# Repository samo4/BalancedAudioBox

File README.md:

# BalancedAudioBox

USB connected balanced +4dBu DAC. Also USB powered. And allegedly 384kHz/32bit.

### Background

I have Genelec active speakers that only have balanced +4dBU input. I only use computer (orginally Intel NUC) as source and I wanted a DAC without any extra wires. There are many comercially availible DAC's, but the selection with balanced output is limited and I also wanted USB powered one without any extra features.

### Status

The first prototype is working great, documentation is under construction.

## How to make one

It's an electronics project, so you can use gerbers to make boards, buy components at your favourite distributor, buy [USB to I2S board](https://amanero.com/) or chinese clone, 3D print the enclosure and assemble everything.

STEP files are included, and here's [the link](https://a360.co/3yRnoUF) to Fusion.

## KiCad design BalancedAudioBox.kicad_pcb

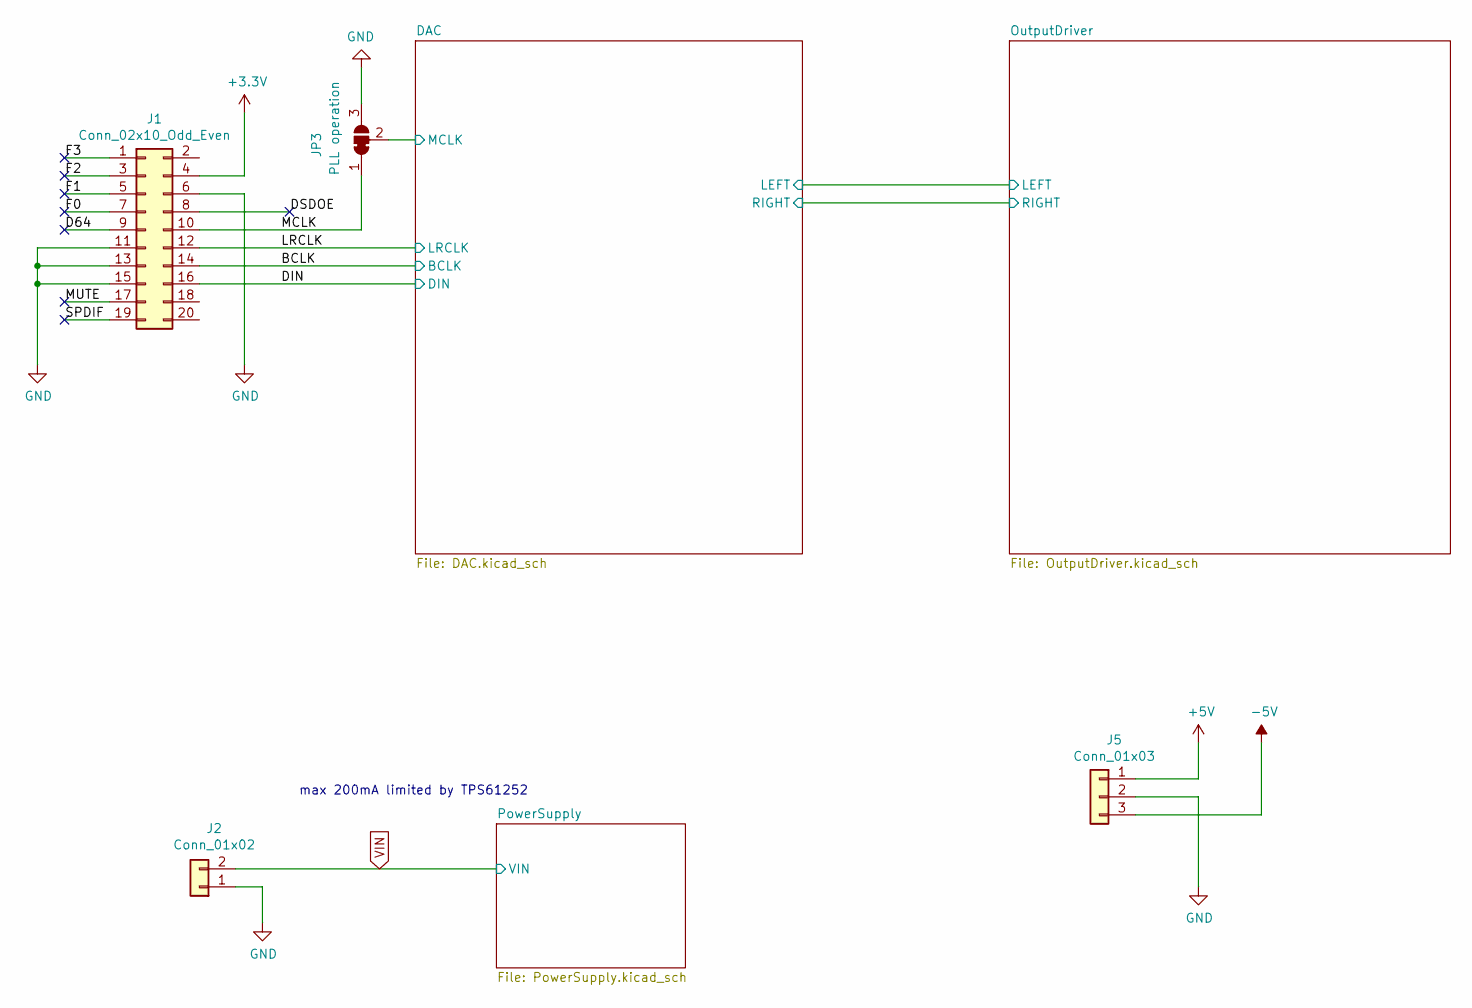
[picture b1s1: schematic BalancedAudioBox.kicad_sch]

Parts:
J1: Conn_02x10_Odd_Even; XMOS_USB_Board_2x10_P2.54mm
J2: Conn_01x02; PinHeader_1x02_P2.54mm_Vertical
J5: Conn_01x03; PinHeader_1x03_P2.54mm_Vertical
JP3: PLL operation; SolderJumper-3_P1.3mm_Bridged12_Pad1.0x1.5mm

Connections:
+3V3: J1.4; also elsewhere on the board
+5V: J5.1; also elsewhere on the board
-5V: J5.3; also elsewhere on the board
/BCLK: J1.14; also elsewhere on the board
/D64: J1.9
/DAC/MCLK: JP3.2 (C); also elsewhere on the board
/DIN: J1.16; also elsewhere on the board
/DSDOE: J1.8
/F0: J1.7
/F1: J1.5
/F2: J1.3
/F3: J1.1
/LRCLK: J1.12; also elsewhere on the board
/MCLK: J1.10, JP3.1 (A)
/MUTE: J1.17
/SPDIF: J1.19
GND: J1.6, J1.11, J1.13, J1.15, J2.1, J5.2, JP3.3 (B); also elsewhere on the board
VIN: J2.2; also elsewhere on the board

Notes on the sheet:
max 200mA limited by TPS61252

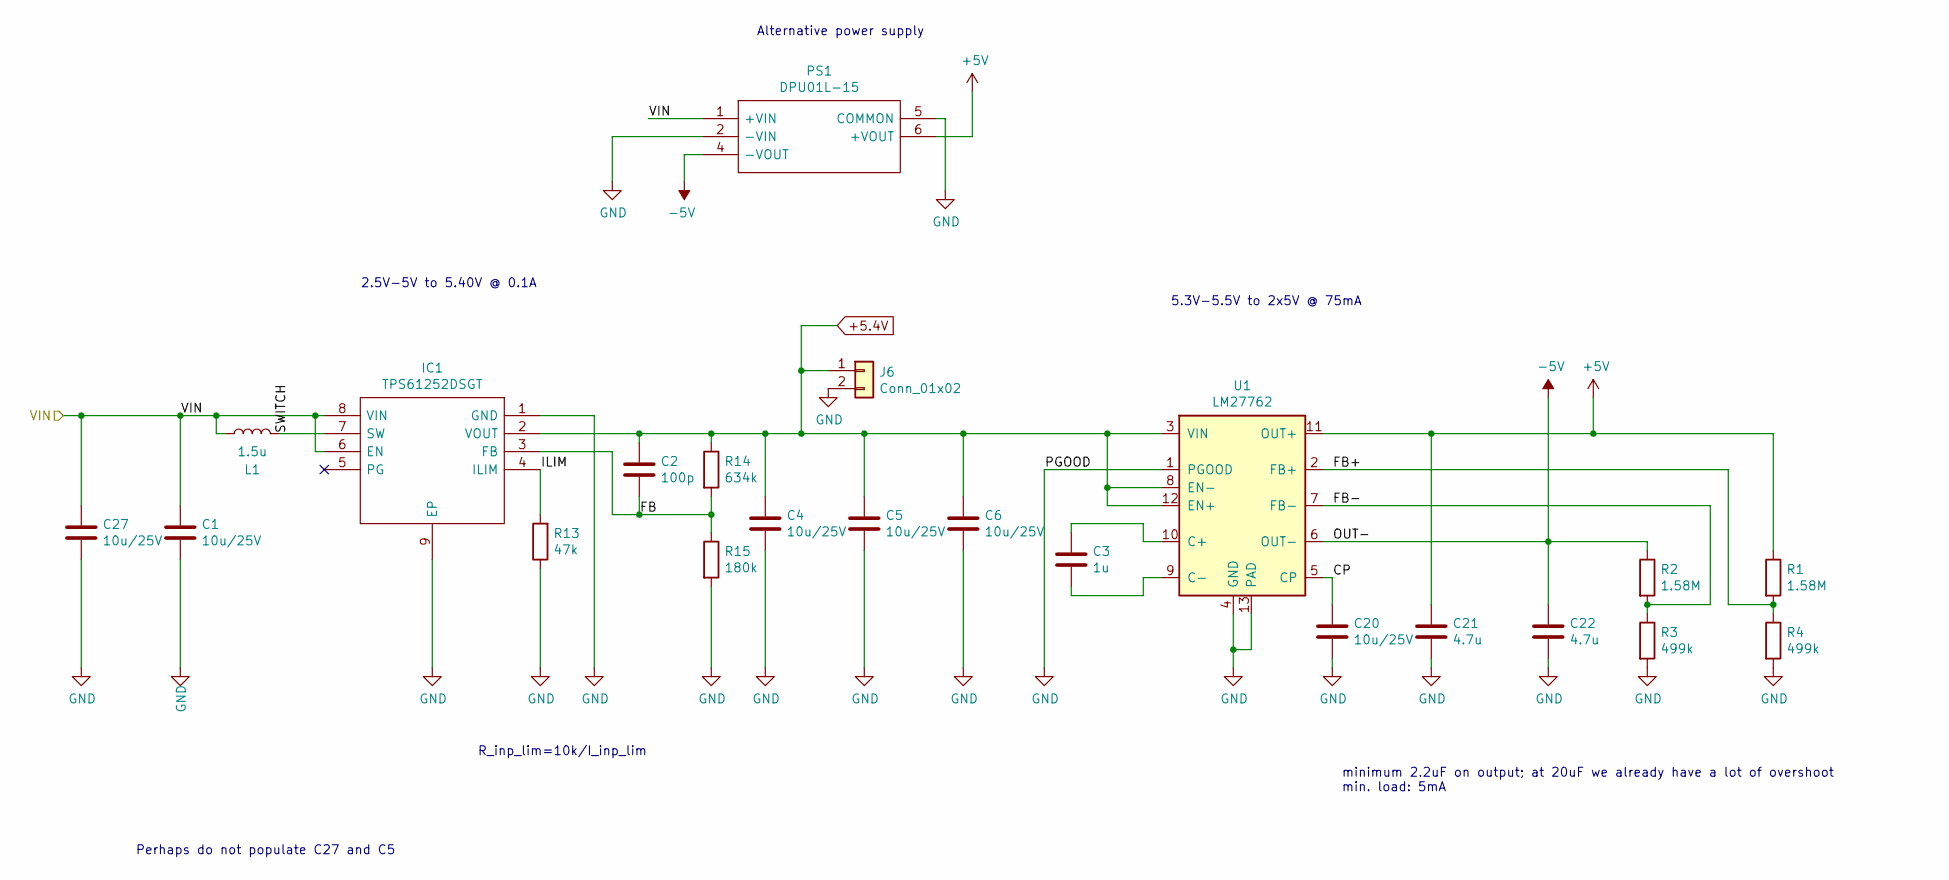
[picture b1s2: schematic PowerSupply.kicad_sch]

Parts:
C1, C4, C5, C6, C20, C27: 10u/25V; C_0805_2012Metric
C2: 100p; C_0603_1608Metric
C3: 1u; C_0402_1005Metric
C21, C22: 4.7u; C_0603_1608Metric
IC1: TPS61252DSGT; SON50P200X200X80-9N; Manufacturer_Part_Number TPS61252DSGT; Mouser Part Number 595-TPS61252DSGT
J6: Conn_01x02; PinHeader_1x02_P2.54mm_Vertical
L1: 1.5u; SRN30151R5Y
PS1: DPU01L-15; DPU01L15; Manufacturer_Part_Number DPU01L-15; Mouser Part Number 709-DPU01L-15
R1, R2: 1.58M; R_0402_1005Metric
R3, R4: 499k; R_0402_1005Metric
R13: 47k; R_0402_1005Metric
R14: 634k; R_0402_1005Metric
R15: 180k; R_0402_1005Metric
U1: LM27762; WSON-12-1EP_3x2mm_P0.5mm_EP1x2.65_ThermalVias

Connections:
+5.4V: C2.1, C4.1, C5.1, C6.1, IC1.2 (VOUT), J6.1, R14.1, U1.3 (VIN), U1.8 (EN-), U1.12 (EN+); also elsewhere on the board
+5V: C21.1, PS1.6 (+VOUT), R1.1, U1.11 (OUT+); also elsewhere on the board
-5V: C22.1, PS1.4 (-VOUT), R2.1, U1.6 (OUT-); also elsewhere on the board
/PowerSupply/CP: C20.1, U1.5 (CP)
/PowerSupply/FB: C2.2, IC1.3 (FB), R14.2, R15.1
/PowerSupply/FB+: R1.2, R4.1, U1.2 (FB+)
/PowerSupply/FB-: R2.2, R3.1, U1.7 (FB-)
/PowerSupply/ILIM: IC1.4 (ILIM), R13.2
/PowerSupply/SWITCH: IC1.7 (SW), L1.2
GND: C1.2, C4.2, C5.2, C6.2, C20.2, C21.2, C22.2, C27.2, IC1.1 (GND), IC1.9 (EP), J6.2, PS1.2 (-VIN), PS1.5 (COMMON), R3.2, R4.2, R13.1, R15.2, U1.1 (PGOOD), U1.4 (GND), U1.13 (PAD); also elsewhere on the board
unnamed: C3.1, U1.10 (C+)
unnamed: C3.2, U1.9 (C-)
VIN: C1.1, C27.1, IC1.6 (EN), IC1.8 (VIN), L1.1, PS1.1 (+VIN); also elsewhere on the board

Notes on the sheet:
5.3V-5.5V to 2x5V @ 75mA
R_inp_lim=10k/I_inp_lim
Perhaps do not populate C27 and C5
2.5V-5V to 5.40V @ 0.1A
Alternative power supply
minimum 2.2uF on output; at 20uF we already have a lot of overshoot min. load: 5mA

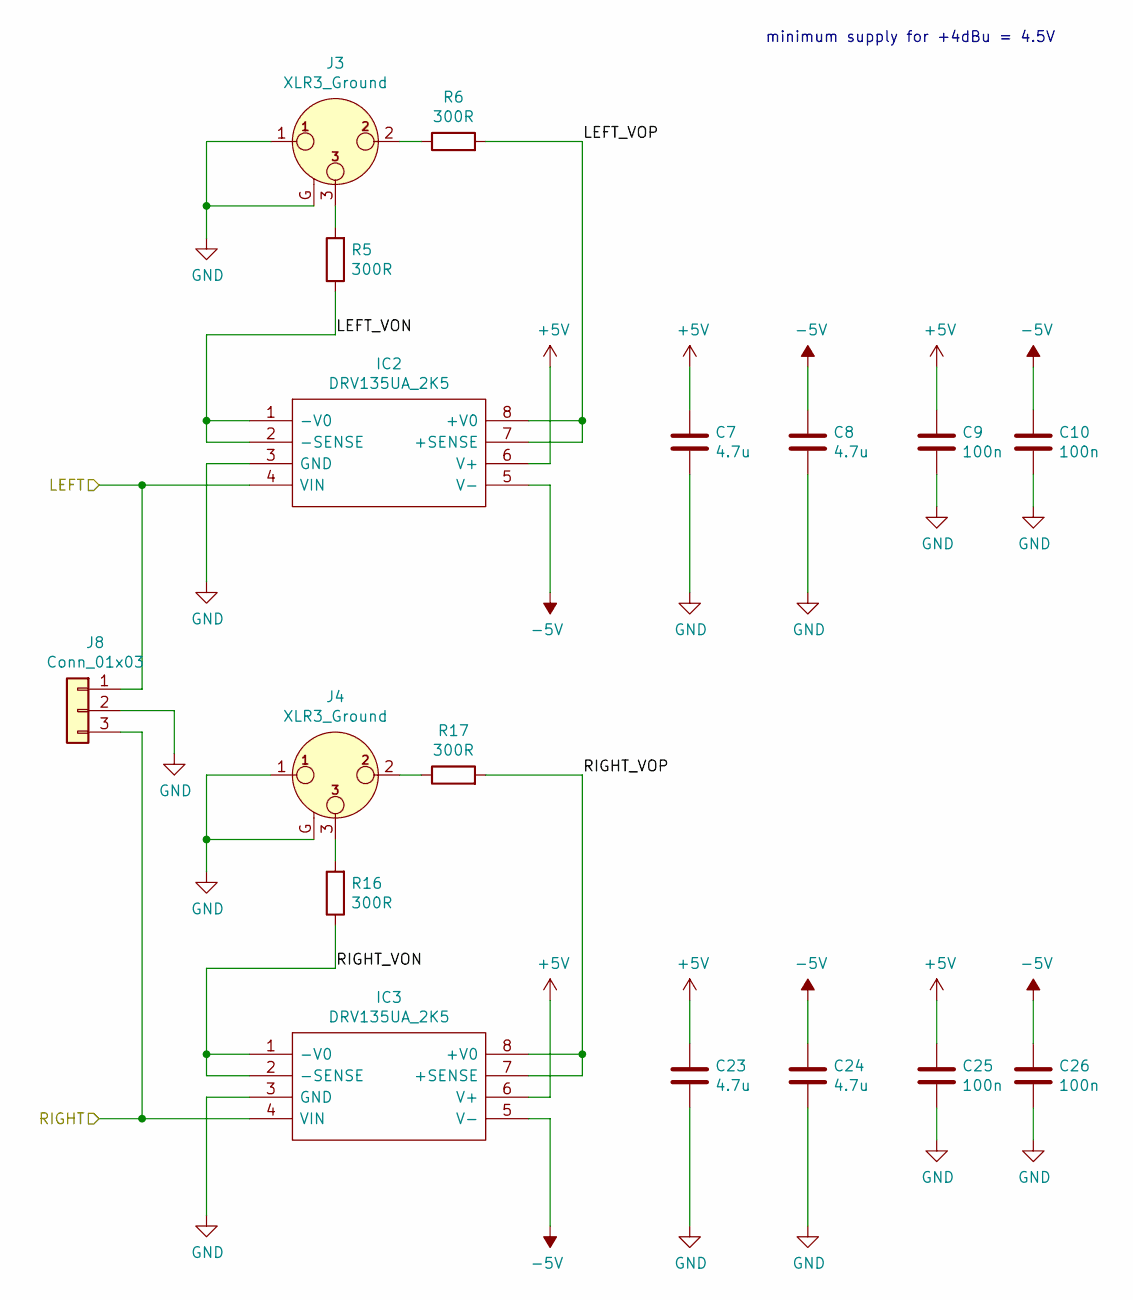
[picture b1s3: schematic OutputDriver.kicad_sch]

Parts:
C7, C8, C23, C24: 4.7u; C_0603_1608Metric
C9, C10, C25, C26: 100n; C_0402_1005Metric
IC2, IC3: DRV135UA_2K5; SOIC-8_3.9x4.9mm_P1.27mm; Manufacturer_Part_Number DRV135UA/2K5; Mouser Part Number 595-DRV135UA/2K5
J3, J4: XLR3_Ground; XLR-NC3MA
J8: Conn_01x03; PinHeader_1x03_P2.54mm_Vertical
R5, R6, R16, R17: 300R; R_0603_1608Metric

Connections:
+5V: C7.1, C9.1, C23.1, C25.1, IC2.6 (V+), IC3.6 (V+); also elsewhere on the board
-5V: C8.1, C10.1, C24.1, C26.1, IC2.5 (V-), IC3.5 (V-); also elsewhere on the board
/DAC/LEFT: IC2.4 (VIN), J8.1; also elsewhere on the board
/DAC/RIGHT: IC3.4 (VIN), J8.3; also elsewhere on the board
/OutputDriver/LEFT_VON: IC2.1 (-V0), IC2.2 (-SENSE), R5.1
/OutputDriver/LEFT_VOP: IC2.7 (+SENSE), IC2.8 (+V0), R6.2
/OutputDriver/RIGHT_VON: IC3.1 (-V0), IC3.2 (-SENSE), R16.1
/OutputDriver/RIGHT_VOP: IC3.7 (+SENSE), IC3.8 (+V0), R17.2
GND: C7.2, C8.2, C9.2, C10.2, C23.2, C24.2, C25.2, C26.2, IC2.3 (GND), IC3.3 (GND), J3.1, J3.G, J4.1, J4.G, J8.2; also elsewhere on the board
unnamed: J3.2, R6.1
unnamed: J3.3, R5.2
unnamed: J4.2, R17.1
unnamed: J4.3, R16.2

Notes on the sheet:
minimum supply for +4dBu = 4.5V

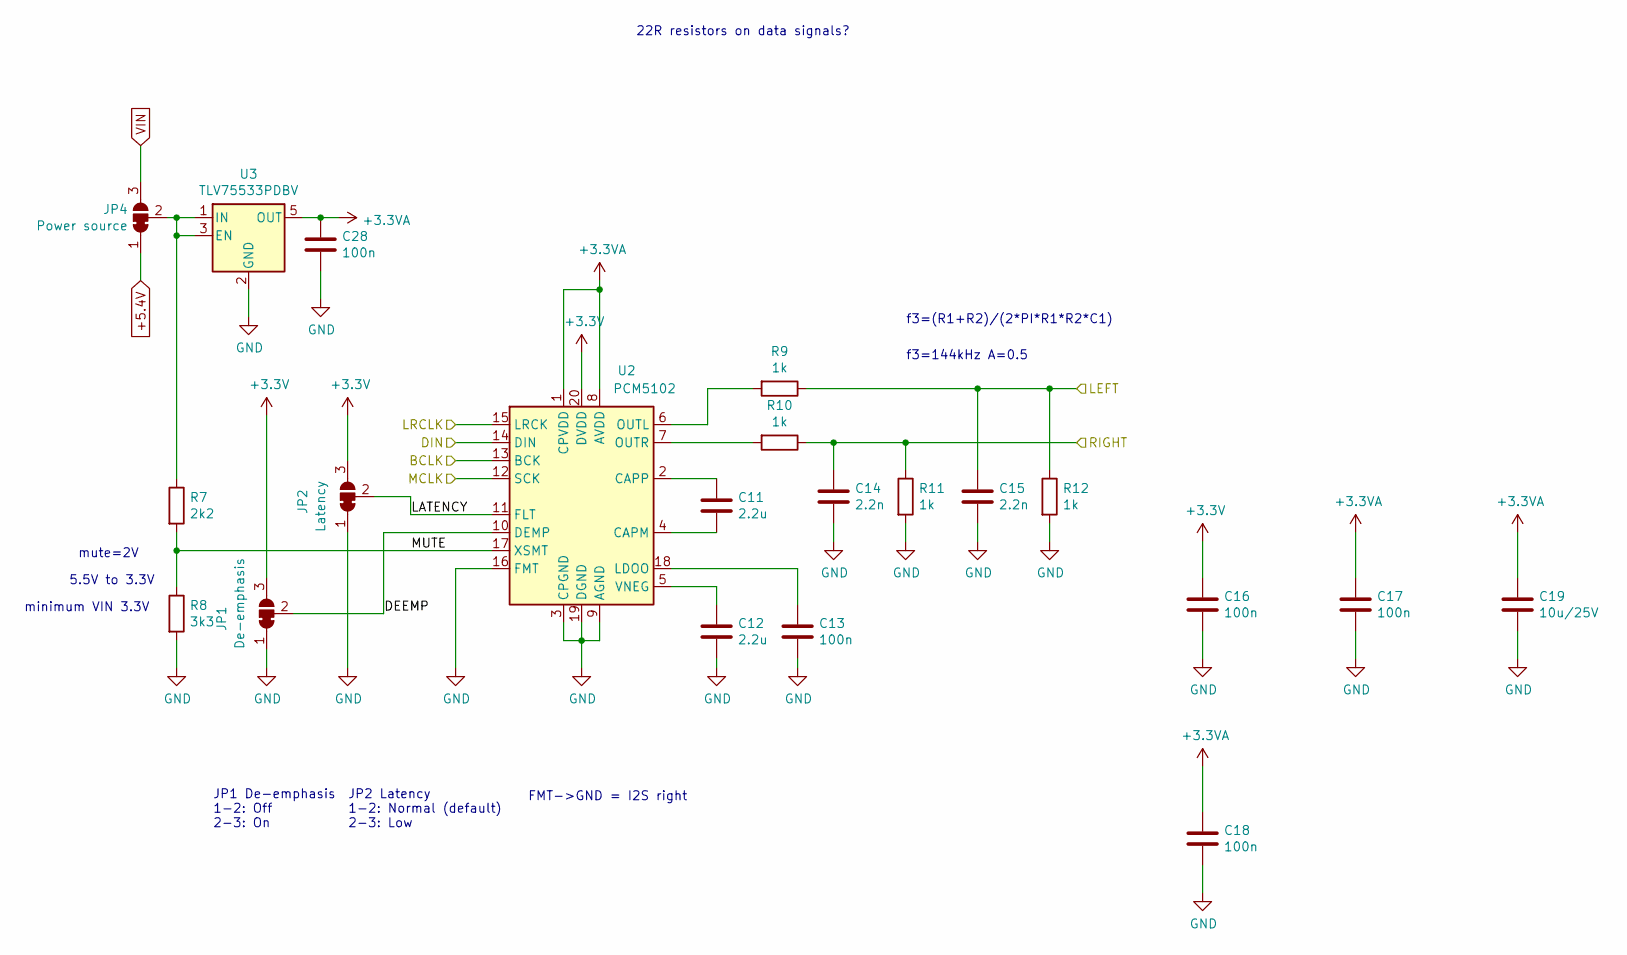
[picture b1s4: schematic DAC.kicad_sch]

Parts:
C11, C12: 2.2u; C_0805_2012Metric
C13, C16, C17, C18, C28: 100n; C_0402_1005Metric
C14, C15: 2.2n; C_0402_1005Metric
C19: 10u/25V; C_0805_2012Metric
JP1: De-emphasis; SolderJumper-3_P1.3mm_Bridged12_Pad1.0x1.5mm
JP2: Latency; SolderJumper-3_P1.3mm_Bridged12_Pad1.0x1.5mm
JP4: Power source; SolderJumper-3_P1.3mm_Bridged12_Pad1.0x1.5mm
R7: 2k2; R_0402_1005Metric
R8: 3k3; R_0402_1005Metric
R9, R10, R11, R12: 1k; R_0402_1005Metric
U2: PCM5102; TSSOP-20_4.4x6.5mm_P0.65mm
U3: TLV75533PDBV; SOT-23-5

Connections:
+3.3VA: C17.1, C18.1, C19.1, C28.1, U2.1 (CPVDD), U2.8 (AVDD), U3.5 (OUT)
+3V3: C16.1, JP1.3 (B), JP2.3 (B), U2.20 (DVDD); also elsewhere on the board
+5.4V: JP4.1 (A); also elsewhere on the board
/BCLK: U2.13 (BCK); also elsewhere on the board
/DAC/DEEMP: JP1.2 (C), U2.10 (DEMP)
/DAC/LATENCY: JP2.2 (C), U2.11 (FLT)
/DAC/LEFT: C15.1, R9.1, R12.1; also elsewhere on the board
/DAC/MCLK: U2.12 (SCK); also elsewhere on the board
/DAC/MUTE: R7.2, R8.1, U2.17 (XSMT)
/DAC/RIGHT: C14.1, R10.1, R11.1; also elsewhere on the board
/DIN: U2.14 (DIN); also elsewhere on the board
/LRCLK: U2.15 (LRCK); also elsewhere on the board
GND: C12.2, C13.2, C14.2, C15.2, C16.2, C17.2, C18.2, C19.2, C28.2, JP1.1 (A), JP2.1 (A), R8.2, R11.2, R12.2, U2.3 (CPGND), U2.9 (AGND), U2.16 (FMT), U2.19 (DGND), U3.2 (GND); also elsewhere on the board
unnamed: C11.1, U2.2 (CAPP)
unnamed: C11.2, U2.4 (CAPM)
unnamed: C12.1, U2.5 (VNEG)
unnamed: C13.1, U2.18 (LDOO)
unnamed: JP4.2 (C), R7.1, U3.1 (IN), U3.3 (EN)
unnamed: R9.2, U2.6 (OUTL)
unnamed: R10.2, U2.7 (OUTR)
VIN: JP4.3 (B); also elsewhere on the board

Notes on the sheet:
minimum VIN 3.3V
f3=144kHz A=0.5
mute=2V
JP1 De-emphasis 1-2: Off 2-3: On
5.5V to 3.3V
FMT->GND = I2S right
JP2 Latency 1-2: Normal (default) 2-3: Low
22R resistors on data signals?
f3=(R1+R2)/(2*PI*R1*R2*C1)

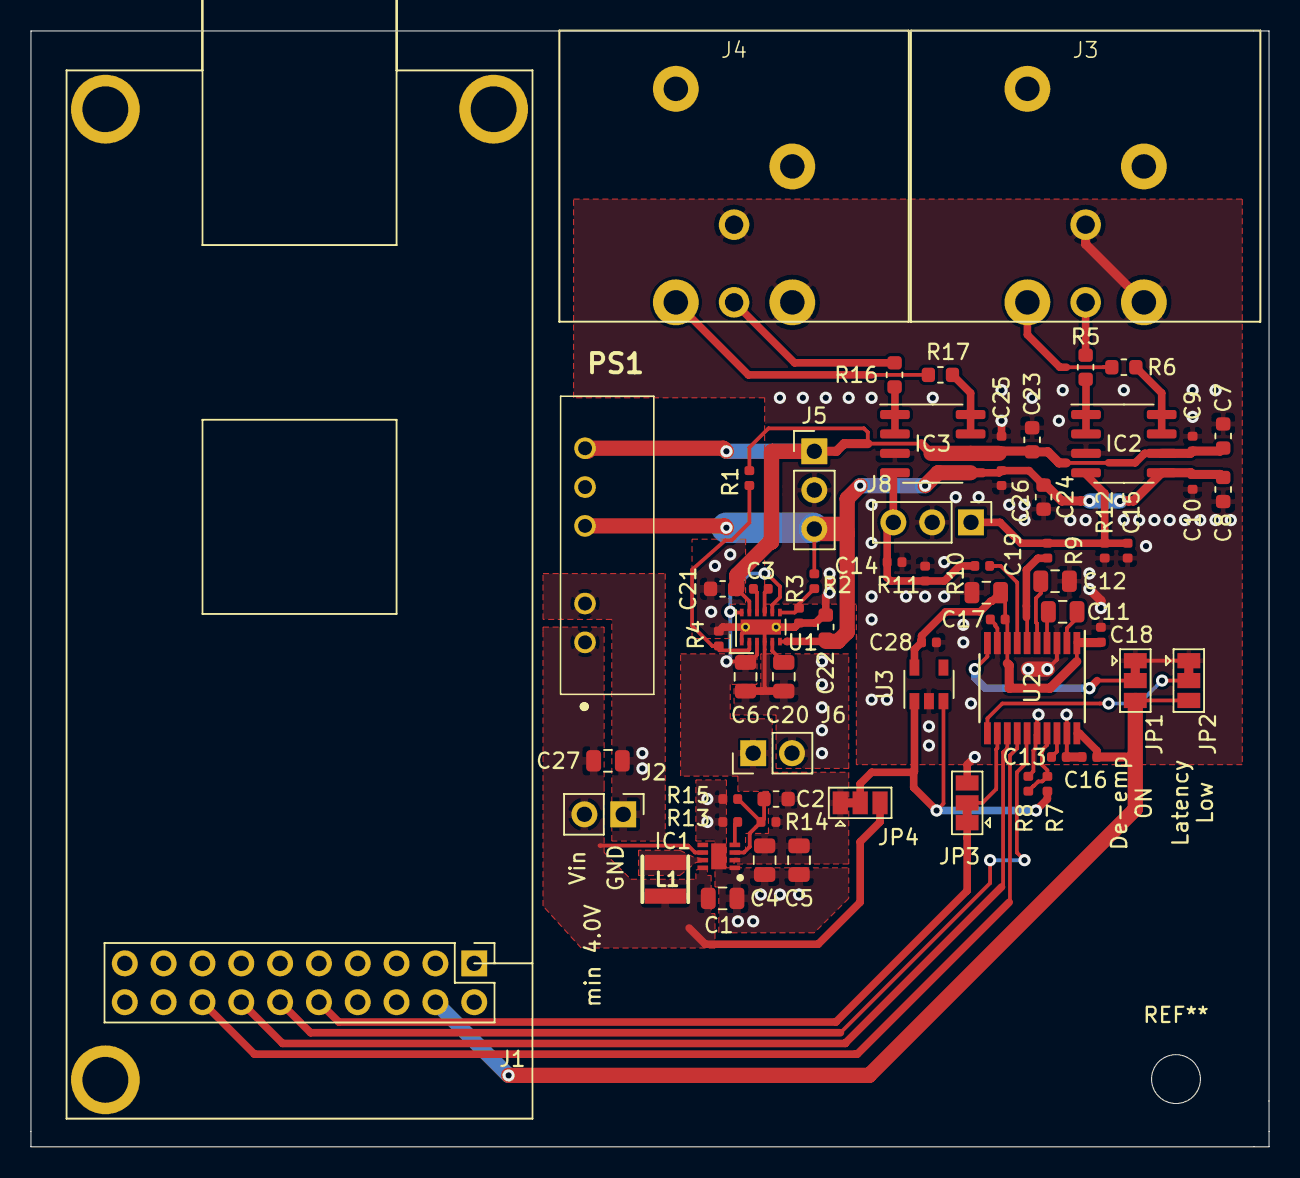
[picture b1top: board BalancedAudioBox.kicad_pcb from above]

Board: 2 copper layers, 81.0 x 73.0 mm, 64 parts (0 on the bottom side), 40 nets.

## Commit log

2019-07-28 selecting actual components
2019-07-30 work
2019-08-01 TPS61252 done
2019-08-01 adding PCB libraries
2019-08-01 ps checked
2019-08-01 placement complete
2019-08-02 footprint and 3d improvements
2019-08-02 layout and silk
2019-08-02 adding regulator
2019-08-02 more layout
2019-11-24 larger conn
2019-11-24 some routing
2019-11-24 sch improv
2019-11-24 full route
2019-12-22 smaller package, drc
2019-12-22 final tweaks
2019-12-22 fix silk
2019-12-23 smth
2019-12-30 solder paste at 90%; changed LDO
2021-09-05 testing links
2021-09-05 improved readme
2021-09-05 adding gerbers (used for first prototype)
2021-09-05 readme
2021-09-05 adding case
2022-01-09 upgrade to 6

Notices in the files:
README.md:
License: BSD 3-Clause
